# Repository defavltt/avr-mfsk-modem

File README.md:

# AVR MFSK (Multiple Frequency Shift Keying) modem transceiver

Original project based on ATmega88/168

Goertzel FFT based tone decoding for noisy audio links

Made specifically for radio use

## Features

 - Serial configurable: base frequency, frequency spacing and rate (~14 bits per second)

 - Repeated transmission of last data sent for performance testing

 - Audio input clipping indication

 - Automatic PTT control output

 - Automatic valid data checking

 - 8-bit sinewave output for regular audio channels

 - Suitable for keyboard-to-keyboard terminal operation

## Operation

There are two modem modes: normal operation / configuration. They are toggled by pressing the button

Configuring the parameters and enabling repeated transmission is done by going into configuration mode and sending a number corresponding to a byte that each of the it's double bits is a parameter value.

| param name | bit position | 0   | 1   | 2    | 3    |
|------------|--------------|-----|-----|------|------|
| rtrans     | 0            | off | on  | -    | -    |
| base freq  | 2            | 375 | 750 | 1125 | 1500 |
| freq space | 4            | 50  | 100 | 150  | 200  |
| rate*      | 6            | 15  | 25  | 35   | 45   |

*the smaller the value the higher the bit rate

Examples:
```
88 > (01 01 10 00) - rtrans off, bf 2, fs 1, r 1
89 > (01 01 10 01) - rtrans on,  bf 2, fs 1, r 1

152 > (10 01 10 00) - rtrans off, bf 2, fs 1, r 2
```

While in configuration mode the LED shows audio input clipping. To set proper input level, a tone from a modem should be played into the input and the level adjusted to where the LED stops flickering. A solid light means too much signal is being fed.

Transmitting data/message is done by sending it by serial in normal operation mode.
Receiving data/message is only done in normal operation mode and retrieved from serial.

LED stays constantly on while: catching a preamble, receiving data/message and transmitting data/message.

_spectral view of the transmission_

## Hardware

The PCB design is made for a 28-pin ATmega (QFN/MLF), whether that's 88, 168, 328, is a personal choice. Single-sided with some jumper wires required, vias are only for ground connection to the bottom layer.

Using an ATmega328 is encouraged, since originally an ATmega88 is used, flash usage is at ~99%, that limits adding more features.

There are pads left on the PCB for ISP programming and future use.

This project uses [MiniCore](https://github.com/MCUdude/MiniCore). Also a 16Mhz crystal is used.

Files for a 3D printed case are included. Case is held together by running a soldering iron along the seam of the top panel and main body.

_modem powered on with a battery and connected with a kenwood style cable_

_bare modem_

_modem with a bluetooth module added_

_toner method etched pcbs_

## Programming

 - Download and install [MiniCore](https://github.com/MCUdude/MiniCore)
 
 - Open code in IDE of choice
 
 - Configure board settings
 
   - Select your MCU and external 16Mhz clock
   
   - Leave the rest of the board settings by default
   
   - If want, you can enable bootloader and leave out a reset pin on the serial connector for future configuring of the key macros.
   
 - Flash via ISP programmer and it's done.

## Things to improve

 - Sometimes data doesn't sync
 - Sample tones more than one time and average them for better results in noisy audio
 - Make a better pwm filtering circuit

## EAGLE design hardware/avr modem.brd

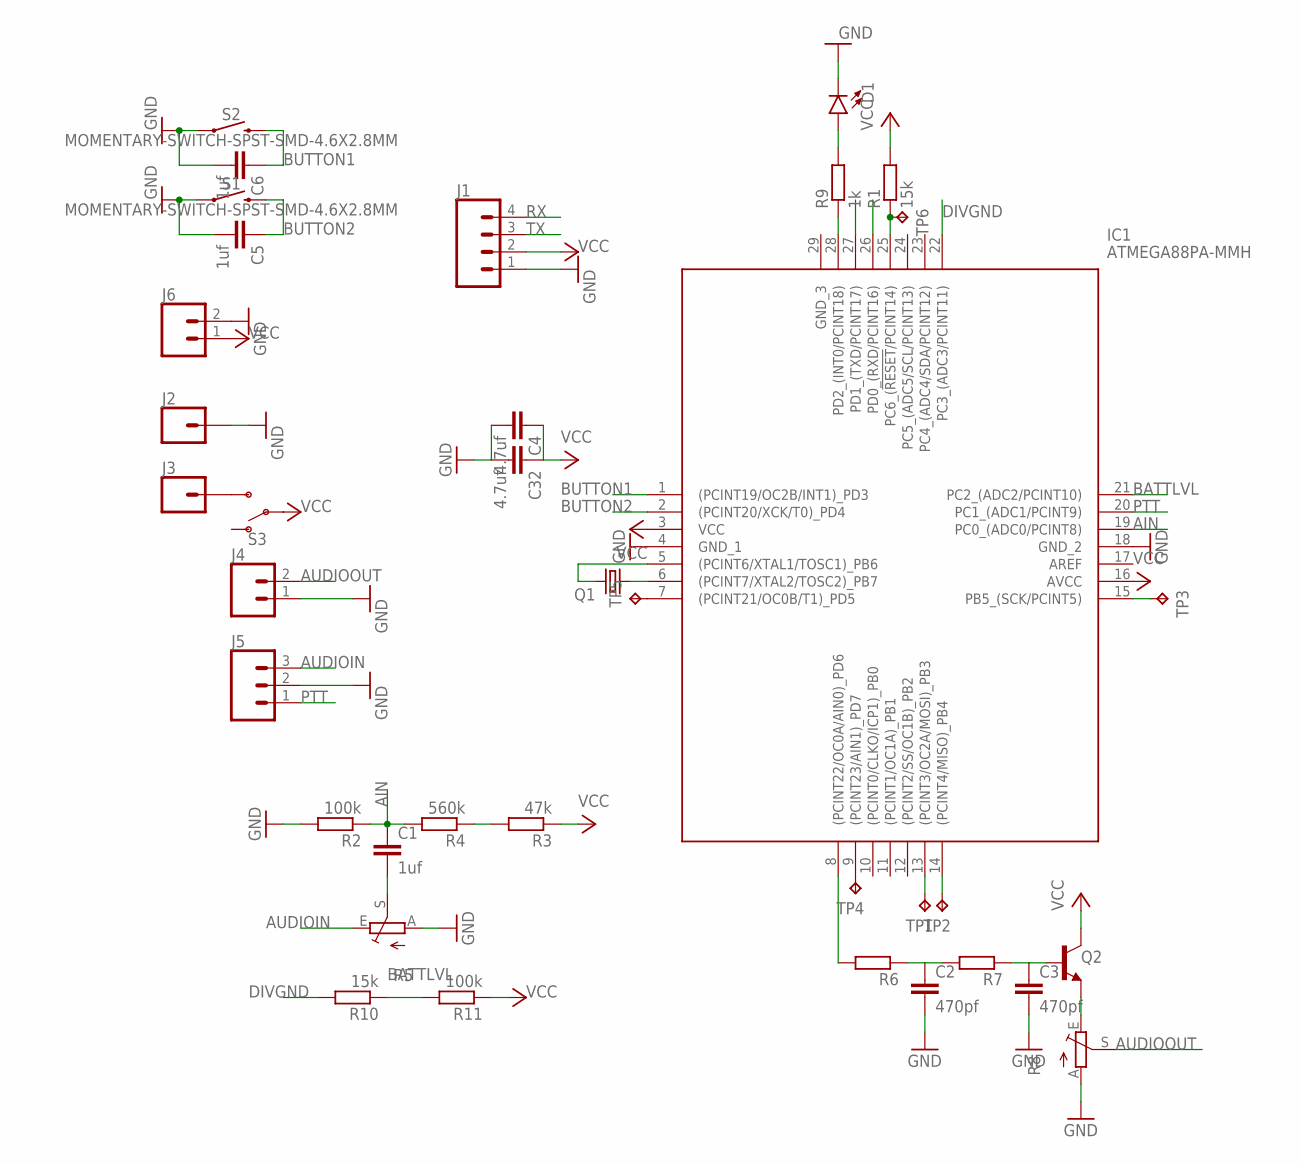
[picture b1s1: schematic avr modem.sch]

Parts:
C1, C5, C6: 1uf; C0805
C2, C3: 470pf; C0805
C4, C32: 4.7uf; C0805
D1: LED0603; LED-0603
IC1: ATMEGA88PA-MMH; QFN45P400X400X100-29N
J1: CONN_04LONGPADS; 1X04_LONGPADS
J2, J3: CONN_01PTH_LONGPAD; 1X01_LONGPAD
J4, J6: CONN_02PTH3; 1X02_LONGPADS
J5: CONN_03LONGPADS; 1X03_LONGPADS
Q1: CRYSTALCTS406; CTS406
Q2: TRANS_NPN-MMBTA42; SOT23-3
R1, R10: 15k; M0805
R2, R11: 100k; M0805
R3: 47k; M0805
R4: 560k; M0805
R5, R8: TRIM_EU-CA6V; CA6V
R6, R7: R-EU_M0805; M0805
R9: 1k; M0805
S1, S2: MOMENTARY-SWITCH-SPST-SMD-4.6X2.8MM; TACTILE_SWITCH_SMD_4.6X2.8MM
S3: SWITCH-SPDT-SMD-RIGHT-ANGLE; SWITCH_SPST_SMD_A
TP1, TP2, TP3, TP4, TP5, TP6: TPTP15R; TP15R

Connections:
AIN: C1.1, IC1.19 (PC0_(ADC0/PCINT8)), R2.1, R4.2
AUDIOIN: J5.3, R5.E
AUDIOOUT: J4.2, R8.S
BATTLVL: IC1.21 (PC2_(ADC2/PCINT10)), R10.1, R11.2
BUTTON1: C6.1, IC1.1 ((PCINT19/OC2B/INT1)_PD3), S2.3 (2), S2.4 (2)
BUTTON2: C5.1, IC1.2 ((PCINT20/XCK/T0)_PD4), S1.3 (2), S1.4 (2)
DIVGND: IC1.22 (PC3_(ADC3/PCINT11)), R10.2
GND: C2.2, C3.2, C4.2, C5.2, C6.2, C32.2, D1.C, IC1.4 (GND_1), IC1.18 (GND_2), J1.1, J2.1, J4.1, J5.2, J6.2, R2.2, R5.A, R8.A, S1.1, S1.2 (1), S2.1, S2.2 (1)
unnamed: IC1.6 ((PCINT7/XTAL2/TOSC2)_PB7), Q1.1
unnamed: IC1.5 ((PCINT6/XTAL1/TOSC1)_PB6), Q1.3 (2)
unnamed: IC1.25 (PC6_(!RESET!/PCINT14)), R1.1, TP6.TP
unnamed: IC1.14 ((PCINT4/MISO)_PB4), TP2.TP
unnamed: IC1.15 (PB5_(SCK/PCINT5)), TP3.TP
unnamed: IC1.13 ((PCINT3/OC2A/MOSI)_PB3), TP1.TP
unnamed: R3.2, R4.1
unnamed: C1.2, R5.S
unnamed: IC1.8 ((PCINT22/OC0A/AIN0)_PD6), R6.2
unnamed: C2.1, R6.1, R7.2
unnamed: C3.1, Q2.1 (B), R7.1
unnamed: IC1.28 (PD2_(INT0/PCINT18)), R9.1
unnamed: D1.A, R9.2
unnamed: J3.1, S3.3 (S)
unnamed: IC1.9 ((PCINT23/AIN1)_PD7), TP4.TP
unnamed: IC1.7 ((PCINT21/OC0B/T1)_PD5), TP5.TP
unnamed: Q2.2 (E), R8.E
PTT: IC1.20 (PC1_(ADC1/PCINT9)), J5.1
RX: IC1.26 (PD0_(RXD/PCINT16)), J1.4
TX: IC1.27 (PD1_(TXD/PCINT17)), J1.3
VCC: C4.1, C32.1, IC1.3 (VCC), IC1.16 (AVCC), J1.2, J6.1, Q2.3 (C), R1.2, R3.1, R11.1, S3.2

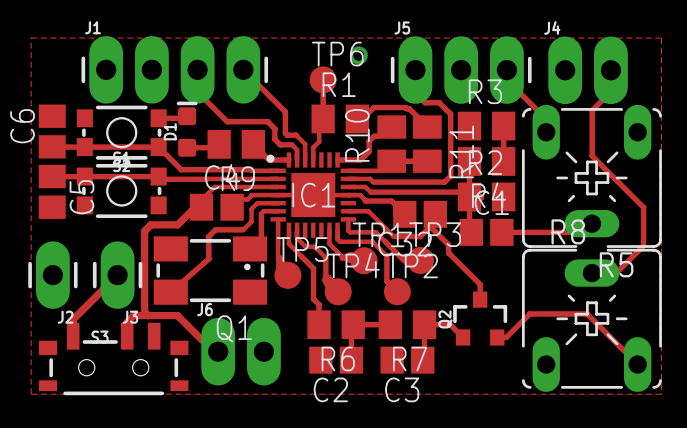
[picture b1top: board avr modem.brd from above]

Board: 2 copper layers, 37 parts (0 on the bottom side), 29 nets.

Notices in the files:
parts and their libraries:
SparkFun-Connectors: Licensing: Creative Commons ShareAlike 4.0 International - https://creativecommons.org/licenses/by-sa/4.0
